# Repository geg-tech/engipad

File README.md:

# EngiPad - The Construction PDA Macropad
> update! i remade the PCB for this macropad in the brand spankin new folder named **ENGIPAD \\\ V2**! this readme and repo currently covers version 1 of the build (which is now finished)

This is a 8-key Hackpad with RGB lighting and an integrated OLED display in the case, modeled after the Engineer's PDA from *Team Fortress 2*. <br/>
[*see it in action in this handy dandy youtube video!*](https://youtu.be/H9Vl-Haxy5c)

The idea came a couple days ago, when I was scrolling through the TF2 wiki and noticed that the PDA would make for a *fire* macropad. I had extra time on hand and was waiting for the parts to come in for my main project, [The Biblically Accurate Keyboard](https://github.com/hunkegg/biblicallyaccuratekeyboard), so I decided to go ahead and try to speedrun designing an actual macropad this time. <br/>
I aimed to be as game accurate as possible, using pictures and screenshots from the game to model and render my case. <br/>

Speaking of the Engineer, I made my macropad work with my custom keybinds for Fusion 360, making tools that I often use like Project and Move more accessible to me while I work on engineering and CAD projects.

Made as part of Hackpad! (and the design competition due in like 4 days lmfao)

### Features!
* 8 keys
* OLED display and RGB
* Custom case and keycaps modeled after the Engineer's Construction PDA
* An alternate CAD file to fit a metal toggle switch I have on hand
* QMK firmware
* TF2 inspired silkscreen on the front and Highway silkscreen on the back
* 5 different key layers, set to keybinds for general use, Discord, Youtube, Minecraft, and Fusion 360

## CAD

 <br/>

> (The CAD for this case is made from scratch for anyone thinking that I just used the TF2 game files; refer to the mile long Fusion timeline and scroll bar below)

## PCB + Schematic

> (note: the back silkscreen in the first PCB view is hidden since it looks very cluttered with it visible)

## BOM

| part | quantity |
|------|------|
| Cherry MX Switches | 8 |
| SK6812 MINI-E LEDs | 8 |
| 0.91 inch OLED display | 1 |
| M3 16mm Screws | 4 |
| Seeed Studio XIAO RP2040 | 1 |
| Wires (to connect OLED) | 1 |
| 3D Printed Case (all parts) | 1 |
| 3D Printed Keycaps | 8 |
| PCB | 1 |
| Super Glue | 1 | <br/>

note: wires, super glue, and a 3D printer to make the case/keycaps are already owned! <br/>

## extras

### Credit and Thanks
* Huge credit to [@samliu's Squarepad](https://github.com/samdev-7/squarepad/tree/main)! Their slot design for the OLED inspired a good chunk of the CAD for this macropad, which is seen in the split apart screen with the OLED sandwiched in between
* A random website online that hosted the model files for the Engineer's PDA models, which allowed me to get accurate reference photos via Blender
* The people behind Highway and Hackpad as always :3

also i couldn't find anywhere to fit a picture of the actual PDA from the game so it goes here

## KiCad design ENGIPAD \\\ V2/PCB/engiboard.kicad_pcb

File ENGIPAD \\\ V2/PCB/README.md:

# the old pcb sucked so i remade it
CHANGES!!!!!!!
* revamped RGB, now with more flashy lights and actually fixed footprints/wiring
* optional encoder, for if you want to replace the decorational rocker switch with something more functional or if you wanna ditch the case entirely
* fixed OLED footprint, now supports direct soldering to the board (idk how i messed this up the first time lmfao)

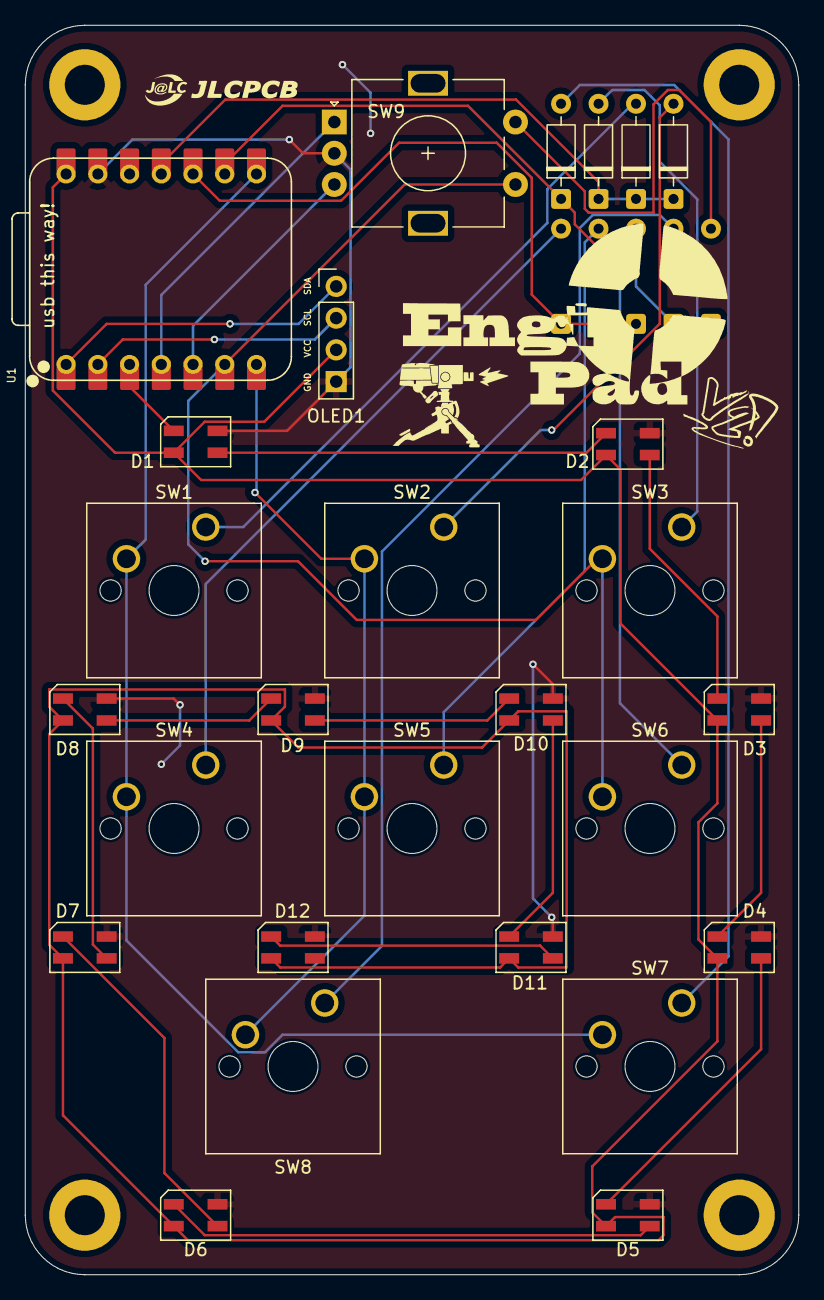
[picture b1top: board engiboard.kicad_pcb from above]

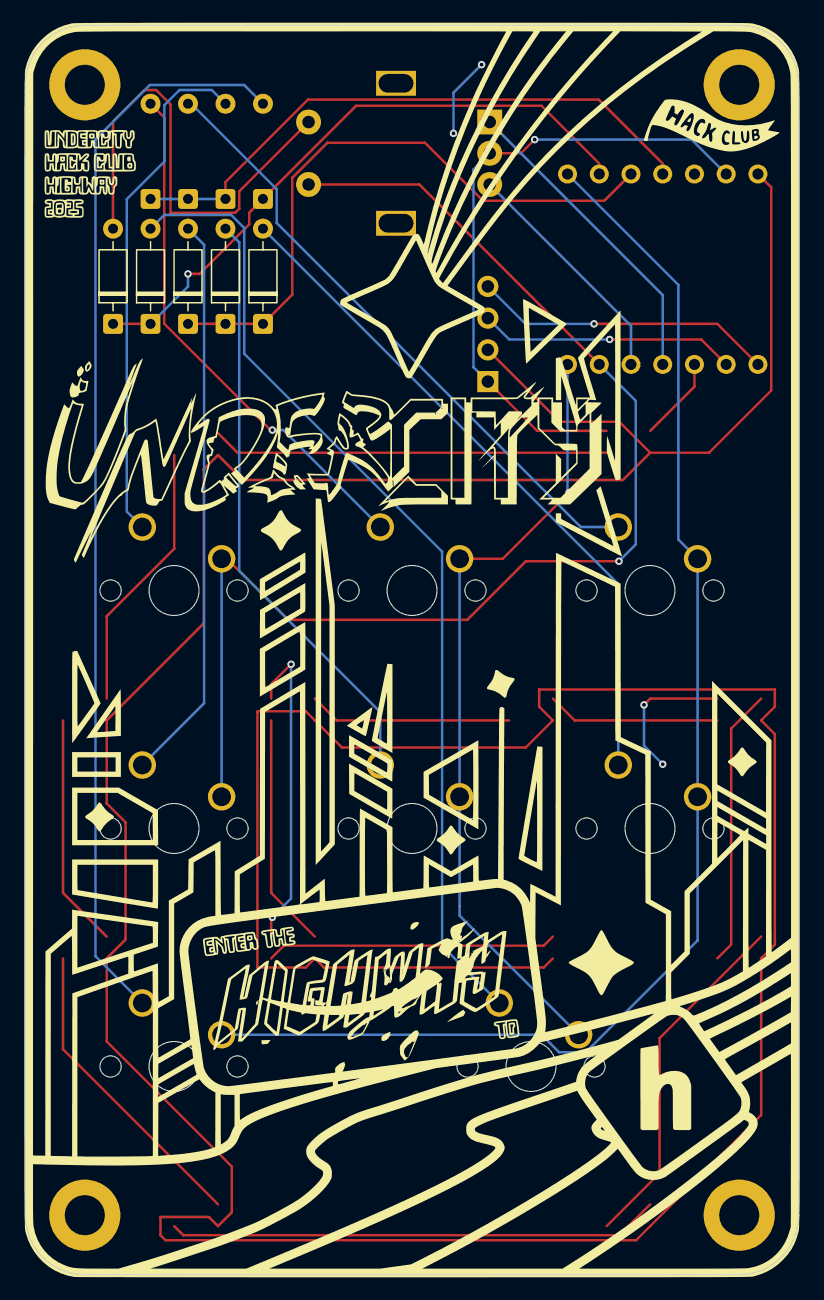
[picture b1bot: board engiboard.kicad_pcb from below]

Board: 2 copper layers, 61.9 x 100.0 mm, 32 parts (5 on the bottom side), 33 nets.

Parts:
D1, D2, D3, D4, D5, D6, D7, D8, D9, D10, D11, D12: SK6812MINI; LED_SK6812MINI_PLCC4_3.5x3.5mm_P1.75mm
D13, D14, D15, D16, D17, D18, D19, D20, D21: 1N4148; D_DO-35_SOD27_P7.62mm_Horizontal
OLED1: PinHeader_1x04_P2.54mm_Vertical
SW1, SW2, SW3, SW4, SW5, SW6, SW7, SW8: SW_Push; SW_Cherry_MX_1.00u_PCB
SW9: RotaryEncoder_Switch; RotaryEncoder_Alps_EC11E-Switch_Vertical_H20mm
U1: XIAO-RP2040-DIP

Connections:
+5V: D1.4 (VDD), D2.4 (VDD), D3.4 (VDD), D4.4 (VDD), D5.4 (VDD), D6.4 (VDD), D7.4 (VDD), D8.4 (VDD), D9.4 (VDD), D10.4 (VDD), D11.4 (VDD), D12.4 (VDD), OLED1.3 (SCL), U1.14 (VBUS)
COL1: SW1.2, SW4.2, SW7.2, U1.8 (GPIO1/RX)
COL2: SW2.2, SW5.2, SW8.2, U1.7 (GPIO0/TX)
COL-KNB: SW3.2, SW6.2, SW9.S1, U1.6 (GPIO7/SCL)
GND: D1.2 (VSS), D2.2 (VSS), D3.2 (VSS), D4.2 (VSS), D5.2 (VSS), D6.2 (VSS), D7.2 (VSS), D8.2 (VSS), D9.2 (VSS), D10.2 (VSS), D11.2 (VSS), D12.2 (VSS), OLED1.4 (SDA), SW9.C, U1.13 (GND)
KNB-A: SW9.A, U1.4 (GPIO29/ADC3/A3)
KNB-B: SW9.B, U1.5 (GPIO6/SDA)
LED: D1.3 (DIN), U1.3 (GPIO28/ADC2/A2)
unnamed: D1.1 (DOUT), D2.3 (DIN)
unnamed: D2.1 (DOUT), D3.3 (DIN)
unnamed: D3.1 (DOUT), D4.3 (DIN)
unnamed: D4.1 (DOUT), D5.3 (DIN)
unnamed: D5.1 (DOUT), D6.3 (DIN)
unnamed: D6.1 (DOUT), D7.3 (DIN)
unnamed: D7.1 (DOUT), D8.3 (DIN)
unnamed: D8.1 (DOUT), D9.3 (DIN)
unnamed: D9.1 (DOUT), D10.3 (DIN)
unnamed: D10.1 (DOUT), D11.3 (DIN)
unnamed: D11.1 (DOUT), D12.3 (DIN)
unnamed: D13.2 (A), SW1.1
unnamed: D14.2 (A), SW2.1
unnamed: D15.2 (A), SW3.1
unnamed: D16.2 (A), SW4.1
unnamed: D17.2 (A), SW5.1
unnamed: D18.2 (A), SW6.1
unnamed: D19.2 (A), SW7.1
unnamed: D20.2 (A), SW8.1
ROW1: D13.1 (K), D14.1 (K), D15.1 (K), U1.11 (GPIO3/MOSI)
ROW2: D16.1 (K), D17.1 (K), D18.1 (K), U1.10 (GPIO4/MISO)
ROW3: D19.1 (K), D20.1 (K), D21.1 (K), U1.9 (GPIO2/SCK)
ROW-KNB: D21.2 (A), SW9.S2
SCL: OLED1.2 (VCC), U1.2 (GPIO27/ADC1/A1)
SDA: OLED1.1 (GND), U1.1 (GPIO26/ADC0/A0)

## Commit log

2025-06-23 Create dsdfdfsd
2025-06-23 Create bl
2025-06-23 Create b
2025-06-25 Create djasdlas
2025-06-25 Create fsdjklf
2025-06-25 Create asdas
